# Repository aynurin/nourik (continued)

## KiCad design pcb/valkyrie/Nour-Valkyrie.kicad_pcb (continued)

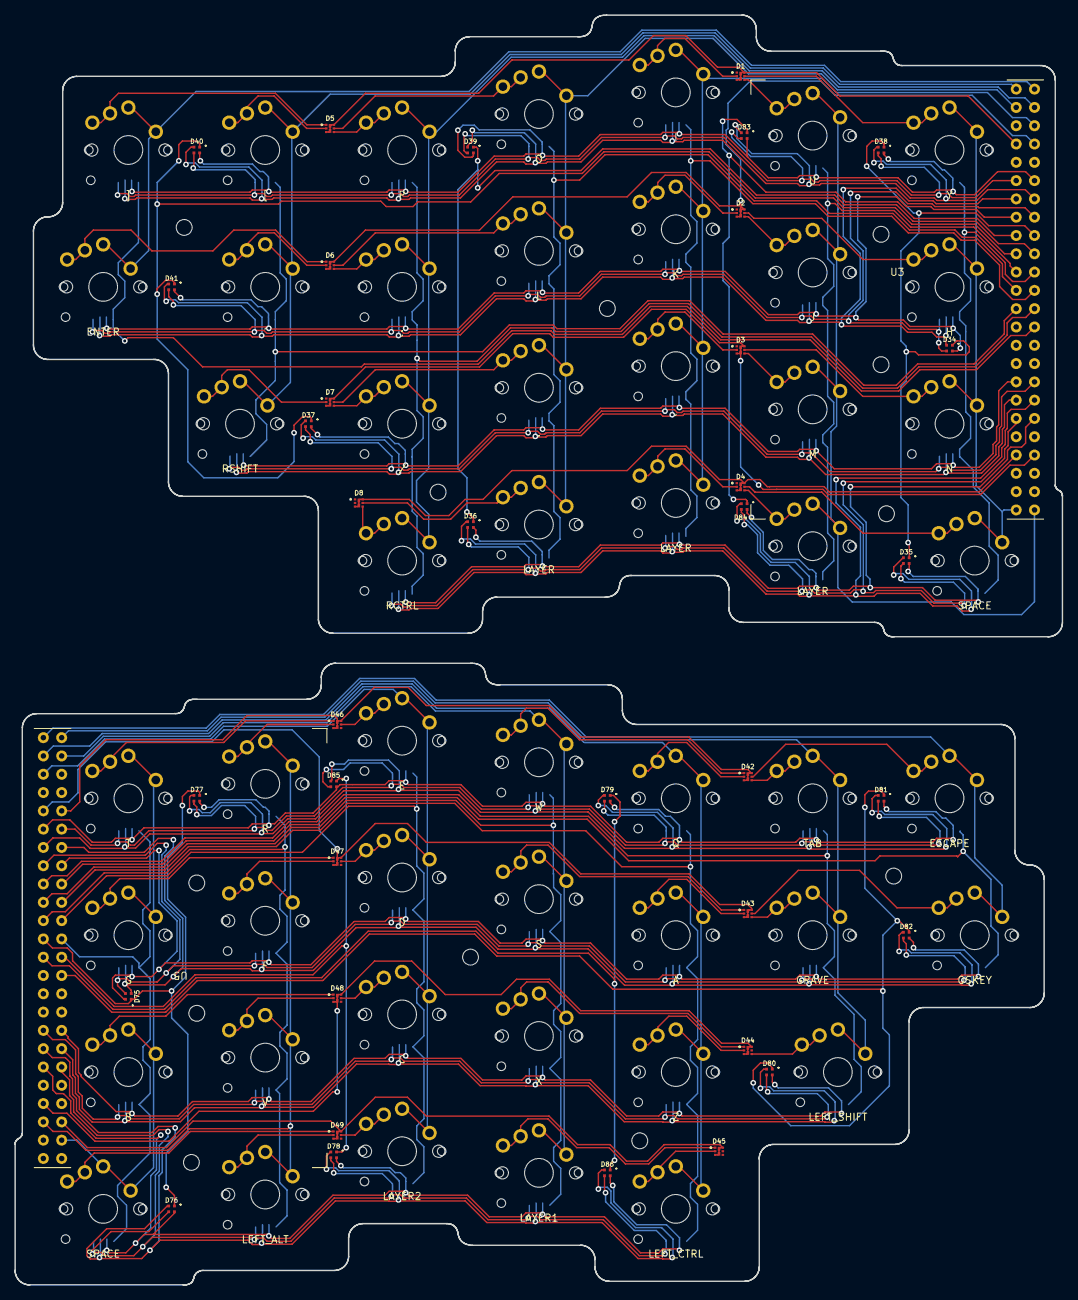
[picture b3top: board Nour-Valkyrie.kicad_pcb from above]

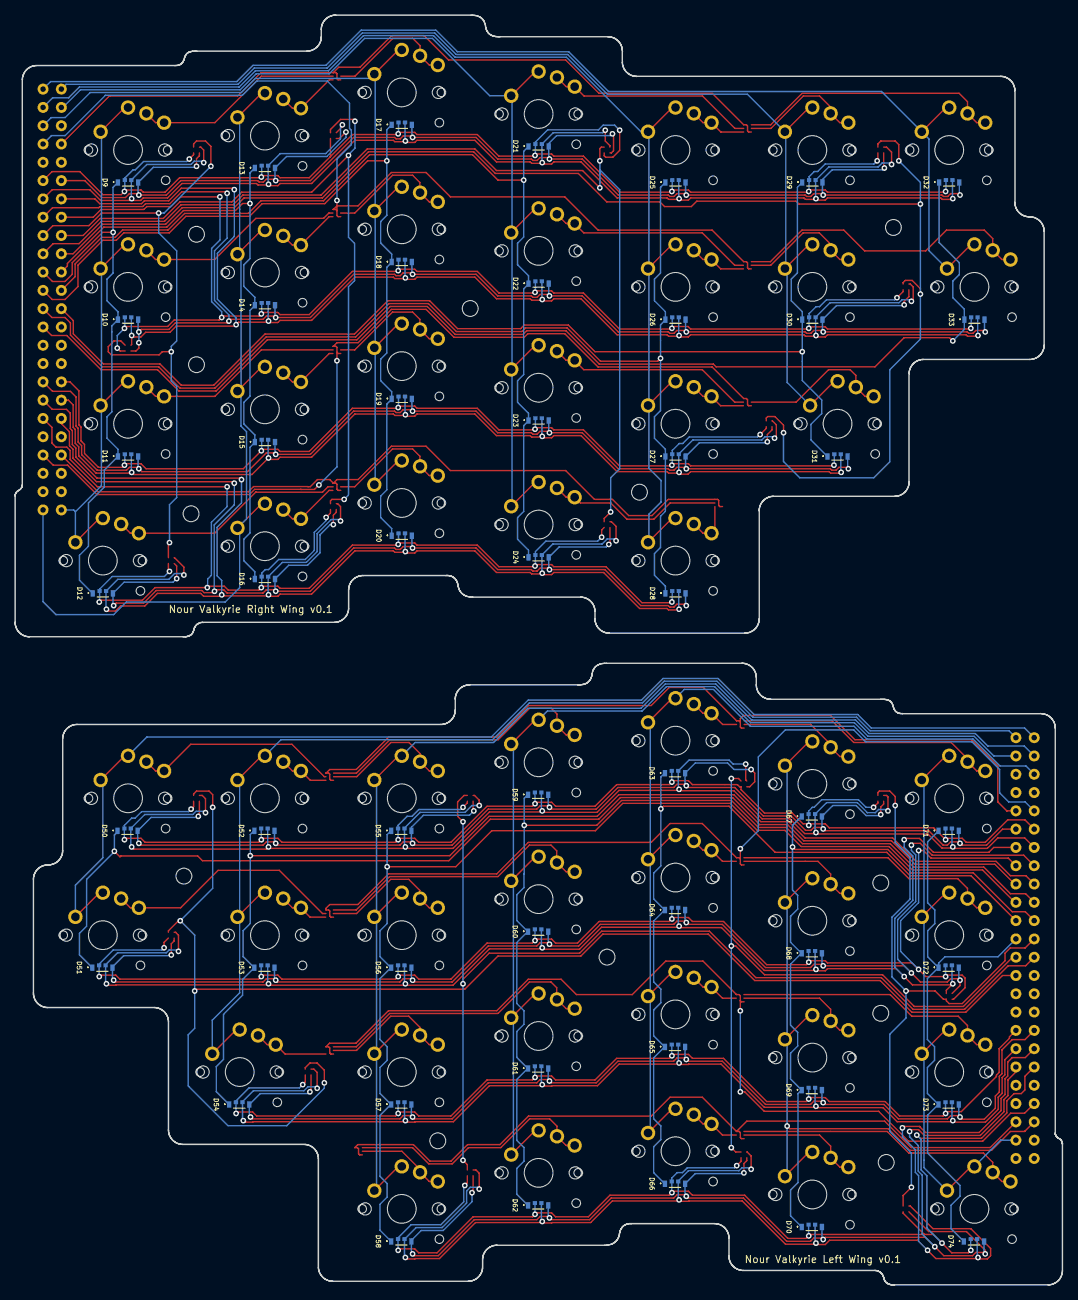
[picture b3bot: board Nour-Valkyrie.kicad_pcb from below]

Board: 2 copper layers, 145.4 x 176.3 mm, 138 parts (50 on the bottom side), 118 nets.

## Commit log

2022-07-07 Initial schematics
2022-07-09 Add RHS schematics sheets
2022-07-15 Draft LHS tracks
2022-07-15 Matrices connection traces
2022-07-15 Initial tracing of the keyboard controller
2022-08-13 Re-traced RHS
2022-08-14 Initial RHS DRC checked
2022-08-21 RHS and LHS wire complete and initial DRC
2022-08-21 Update schematics to match new footprints
2022-08-21 Deal with DRC warnings due to silkscreen clipped by solder mask
2022-08-29 Draft wire the core
2022-09-04 Complete wiring
2022-09-04 Add mounting holes
2022-09-04 Add missing files
2022-09-04 Rename project
2022-09-04 Split the Core into a separate project
2022-09-05 Removed unnecessary files
2022-09-10 v0.1 gerbers
